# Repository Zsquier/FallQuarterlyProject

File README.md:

# FallQuarterlyProject
EAGLE schematic for CPP IEEE variable voltage power supply

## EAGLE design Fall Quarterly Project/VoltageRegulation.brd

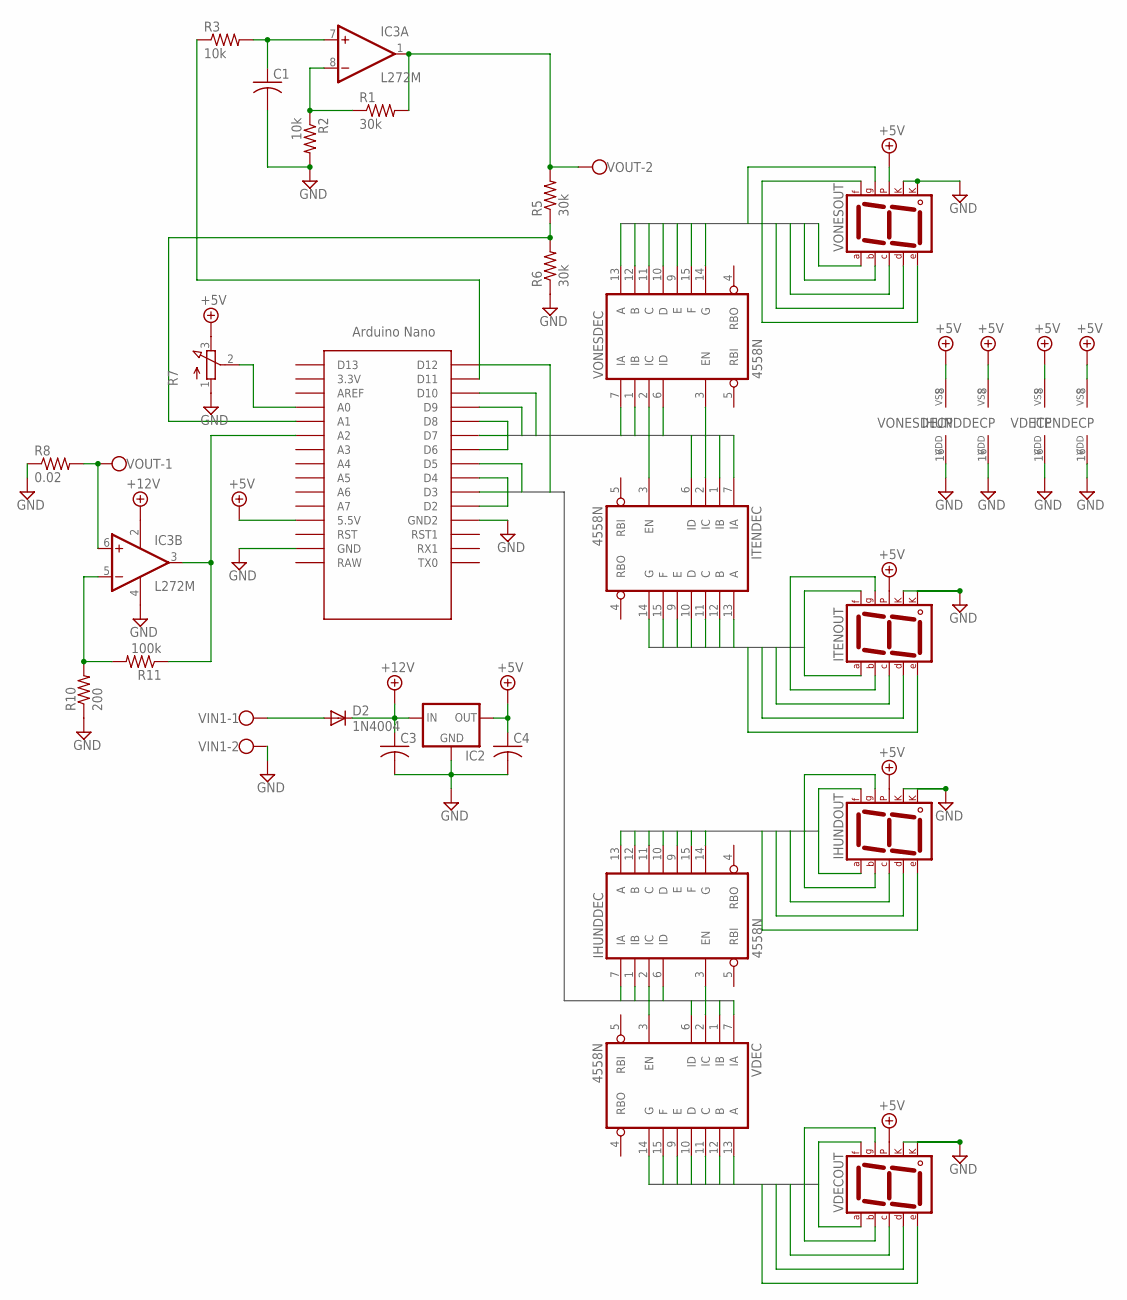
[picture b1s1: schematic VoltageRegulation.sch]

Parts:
C1: C-US050-024X044; C050-024X044
C3, C4: C-US050-055X075; C050-055X075
D2: 1N4004; DO41-10
IC2: 78XXS
IC3: L272M; DIL08
IHUNDDEC: 4558N; DIL16
IHUNDOUT: 7SEG-CK; 7SEG-13
ITENDEC: 4558N; DIL16
ITENOUT: 7SEG-CK; 7SEG-13
R1, R5, R6: 30k; 0207/7
R2, R3: 10k; 0207/7
R7: 3RP/1610N
R8: 0.02; 0411/12
R10: 200; 0207/7
R11: 100k; 0207/7
U$1: NANO
VDEC: 4558N; DIL16
VDECOUT: 7SEG-CK; 7SEG-13
VIN1: W237-102
VONESDEC: 4558N; DIL16
VONESOUT: 7SEG-CK; 7SEG-13
VOUT: W237-102

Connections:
1DIGITBUS1: VONESDEC.13 (A), VONESOUT.7 (A)
1DIGITBUS2: VONESDEC.12 (B), VONESOUT.6 (B)
1DIGITBUS3: VONESDEC.11 (C), VONESOUT.4 (C)
1DIGITBUS4: VONESDEC.10 (D), VONESOUT.2 (D)
1DIGITBUS5: VONESDEC.9 (E), VONESOUT.1 (E)
1DIGITBUS6: VONESDEC.15 (F), VONESOUT.9 (F)
1DIGITBUS7: VONESDEC.14 (G), VONESOUT.10 (G)
1SDIGIT1: ITENDEC.7 (IA), U$1.D6, VONESDEC.7 (IA)
1SDIGIT2: ITENDEC.1 (IB), U$1.D7, VONESDEC.1 (IB)
1SDIGIT3: ITENDEC.2 (IC), U$1.D8, VONESDEC.2 (IC)
1SDIGIT4: ITENDEC.6 (ID), U$1.D9, VONESDEC.6 (ID)
1SDIGIT5: ITENDEC.3 (EN), U$1.D10, VONESDEC.3 (EN)
2DIGIT1: VDEC.13 (A), VDECOUT.7 (A)
2DIGIT2: VDEC.12 (B), VDECOUT.6 (B)
2DIGIT3: VDEC.11 (C), VDECOUT.4 (C)
2DIGIT4: VDEC.10 (D), VDECOUT.2 (D)
2DIGIT5: VDEC.9 (E), VDECOUT.1 (E)
2DIGIT6: VDEC.15 (F), VDECOUT.9 (F)
2DIGIT7: VDEC.14 (G), VDECOUT.10 (G)
4DIGIT1: IHUNDDEC.13 (A), IHUNDOUT.7 (A)
4DIGIT2: IHUNDDEC.12 (B), IHUNDOUT.6 (B)
4DIGIT3: IHUNDDEC.11 (C), IHUNDOUT.4 (C)
4DIGIT4: IHUNDDEC.10 (D), IHUNDOUT.2 (D)
4DIGIT5: IHUNDDEC.9 (E), IHUNDOUT.1 (E)
4DIGIT6: IHUNDDEC.15 (F), IHUNDOUT.9 (F)
4DIGIT7: IHUNDDEC.14 (G), IHUNDOUT.10 (G)
10SDIGIT1: IHUNDDEC.7 (IA), U$1.D2, VDEC.7 (IA)
10SDIGIT2: IHUNDDEC.1 (IB), U$1.D3, VDEC.1 (IB)
10SDIGIT3: IHUNDDEC.2 (IC), U$1.D4, VDEC.2 (IC)
10SDIGIT4: IHUNDDEC.6 (ID), U$1.D5, VDEC.6 (ID)
10SDIGIT5: IHUNDDEC.3 (EN), U$1.D12, VDEC.3 (EN)
+5V: C4.1, IC2.OUT, IHUNDDEC.8 (VSS), IHUNDOUT.5 (DP), ITENDEC.8 (VSS), ITENOUT.5 (DP), R7.3 (E), U$1.5V (5.5V), VDEC.8 (VSS), VDECOUT.5 (DP), VONESDEC.8 (VSS), VONESOUT.5 (DP)
+12V: C3.1, D2.C, IC2.IN, IC3.2 (V+)
GND: C1.2, C3.2, C4.2, IC2.GND, IC3.4 (GND), IHUNDDEC.16 (VDD), IHUNDOUT.3 (CK1), IHUNDOUT.8 (CK2), ITENDEC.16 (VDD), ITENOUT.3 (CK1), ITENOUT.8 (CK2), R2.2, R6.1, R7.1 (A), R8.1, R10.1, U$1.GND, U$1.GND1 (GND2), VDEC.16 (VDD), VDECOUT.3 (CK1), VDECOUT.8 (CK2), VIN1.2, VONESDEC.16 (VDD), VONESOUT.3 (CK1), VONESOUT.8 (CK2)
ITENBUS1: ITENDEC.13 (A), ITENOUT.7 (A)
ITENBUS2: ITENDEC.12 (B), ITENOUT.6 (B)
ITENBUS3: ITENDEC.11 (C), ITENOUT.4 (C)
ITENBUS4: ITENDEC.10 (D), ITENOUT.2 (D)
ITENBUS5: ITENDEC.9 (E), ITENOUT.1 (E)
ITENBUS6: ITENDEC.15 (F), ITENOUT.9 (F)
ITENBUS7: ITENDEC.14 (G), ITENOUT.10 (G)
unnamed: R3.1, U$1.D11
unnamed: IC3.6 (+IN), R8.2, VOUT.1
unnamed: D2.A, VIN1.1
unnamed: IC3.8 (-IN), R1.1, R2.1
unnamed: C1.1, IC3.7 (+IN), R3.2
unnamed: IC3.1 (OUT), R1.2, R5.2, VOUT.2
unnamed: R7.2 (S), U$1.A0
unnamed: IC3.3 (OUT), R11.1, U$1.A2
unnamed: IC3.5 (-IN), R10.2, R11.2
unnamed: R5.1, R6.2, U$1.A1

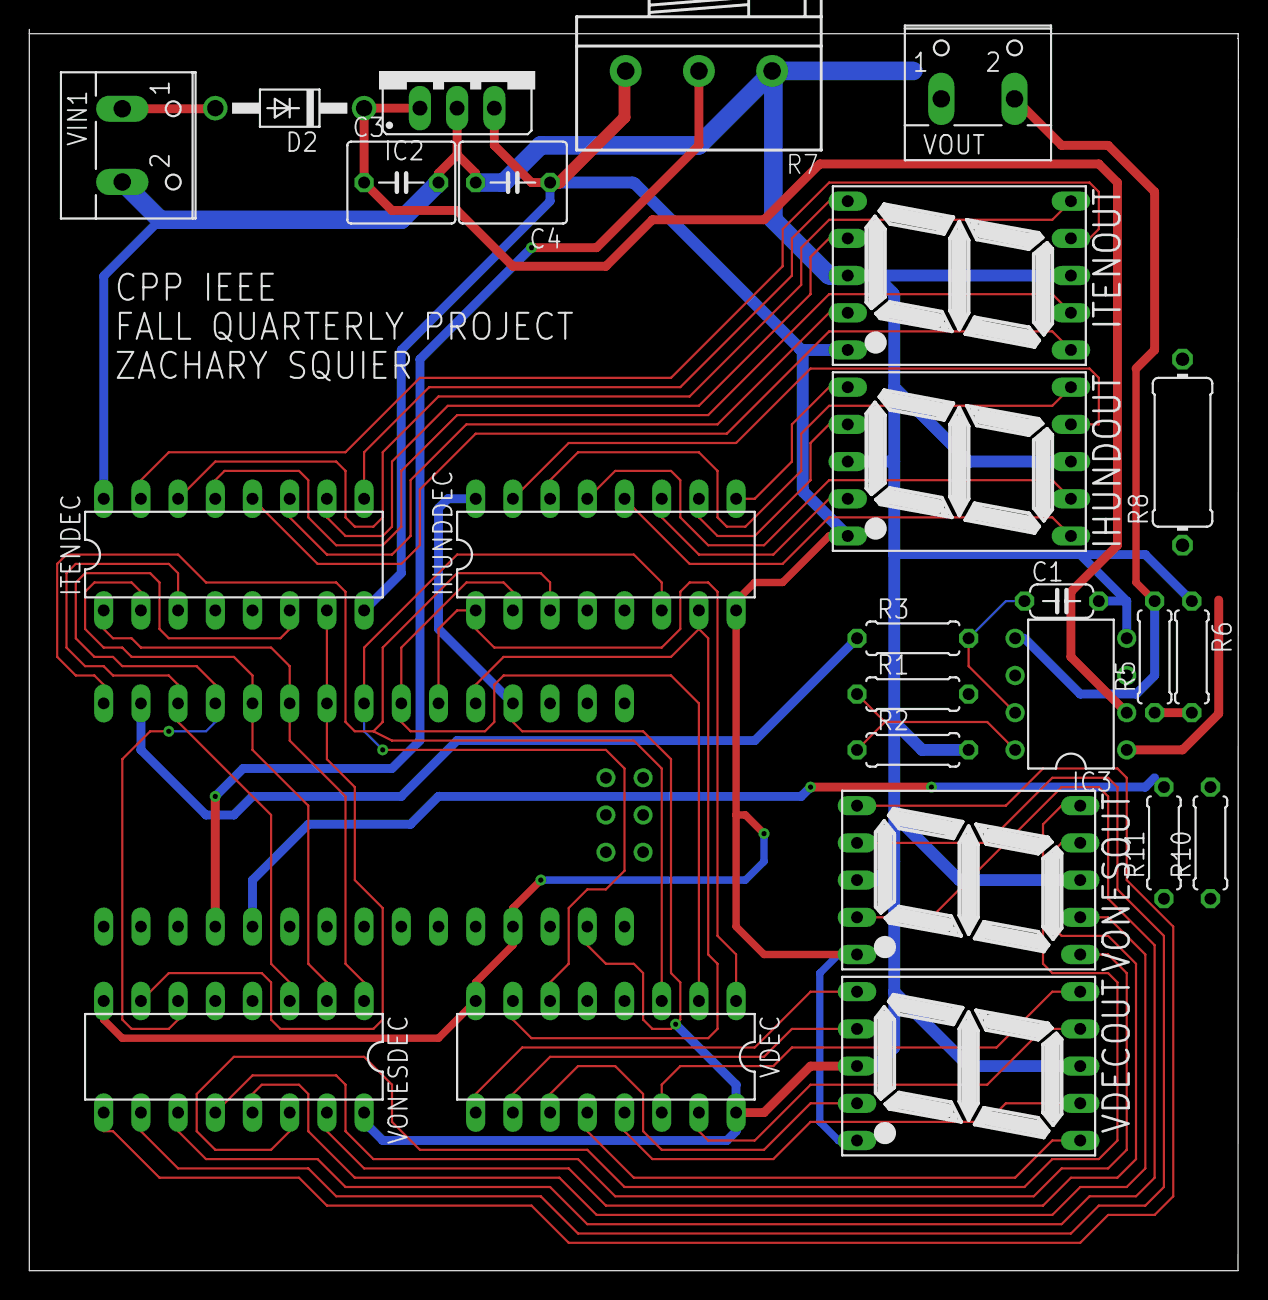
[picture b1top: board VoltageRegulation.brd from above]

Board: 2 copper layers, 82.6 x 84.8 mm, 26 parts (0 on the bottom side), 51 nets.

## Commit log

2017-12-02 Update 1.1
    Added digital circuit to a new sheet in "VoltageRegulation" file, it appears we need the entire schematic in one sheet however. Digital circuit and the arduino were also added. In another folder, I w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
2017-12-02 Update 1.2
    Introduced part of the voltage sense circuitry, filter, and amplifier. most parts still need values though, those of you with r or c values can feel free to label them.
2017-12-06 Update 1.3
    All major parts have now been included in the schematic, only adjustments need to be made now. I know some resistor values have been implemented with series or parallel combinations in order use stoc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
2017-12-06 Update 1.4
    Just began routing the board and deciding where parts will lie. I'm keeping to one layer of the board for now, that way any nets that need to be escaped to another side of the board won't need any cr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
2017-12-06 Update 1.5
    More routing of signals, power traces went down and better organization of support circuitry
2017-12-07 Update 1.5
    Finished routing board, needs work still confirming parts and ensuring layout and schematic are good.
2017-12-24 Update 1.6
    Fixed current sense circuit, just need to update the board layout now
